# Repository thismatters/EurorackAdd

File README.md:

# Simple Add

This simple adder could come from any textbook which introduces op-amp circuits. Really simple, pretty useful too!

The KiCAD project here uses the library/footprints [found in my companion repo](https://github.com/thismatters/EurorackKiCAD).

## Width

7hp on an [Intellijel 1U rack](https://intellijel.com/support/1u-technical-specifications/).

## Inputs

Three signal jacks

## Outputs

One signal jack with the sum of the three inputs

## Vendors

There are part numbers in the [BOM](add.csv) for many of the parts (not for basic passives though) at the following vendors:

* [Mouser](https://www.mouser.com): Needs no introduction. Get your ICs from here (or [digikey](https://www.digikey.com)).
* [Tayda Electronics](https://www.taydaelectronics.com/): Good supplier for passive components; audio jacks, and potentiometers. Their audio jacks are slightly smaller than the thonkiconn from thonk.
* [Love My Switches](https://lovemyswitches.com/): Has [really good knobs](https://lovemyswitches.com/anodized-aluminum-knob-the-lo-fi-1-4-smooth-shaft-12-5mm-od/) to go on those potentiometers!
* [OSHPark](https://oshpark.com/): Fast and (relatively) cheap PCB manufacturer. Prototype run pending.

## Changelog

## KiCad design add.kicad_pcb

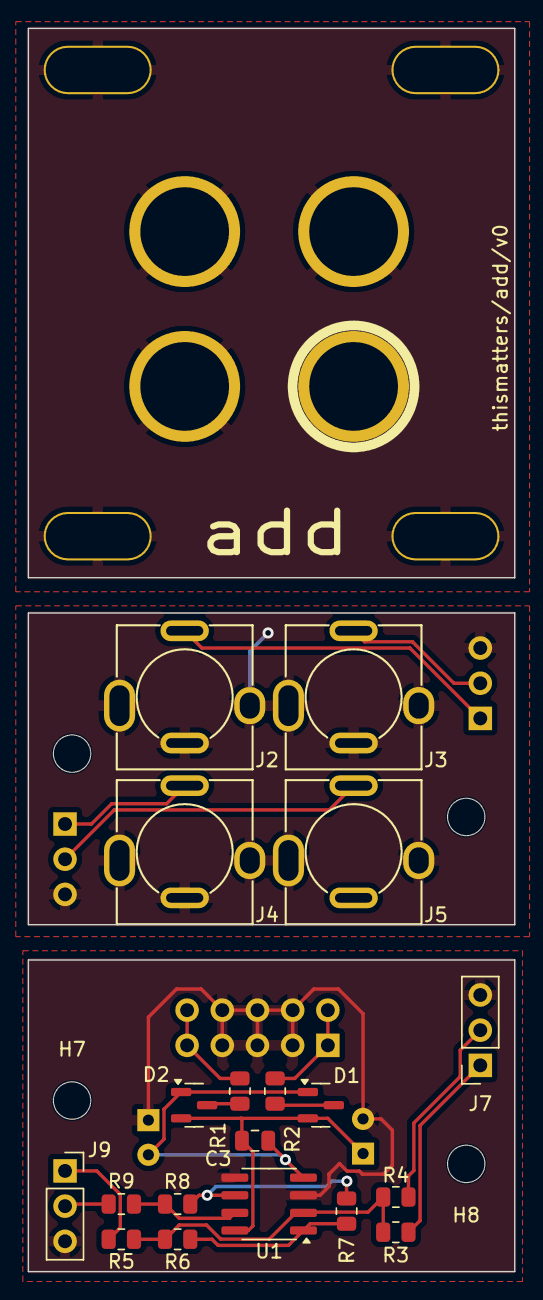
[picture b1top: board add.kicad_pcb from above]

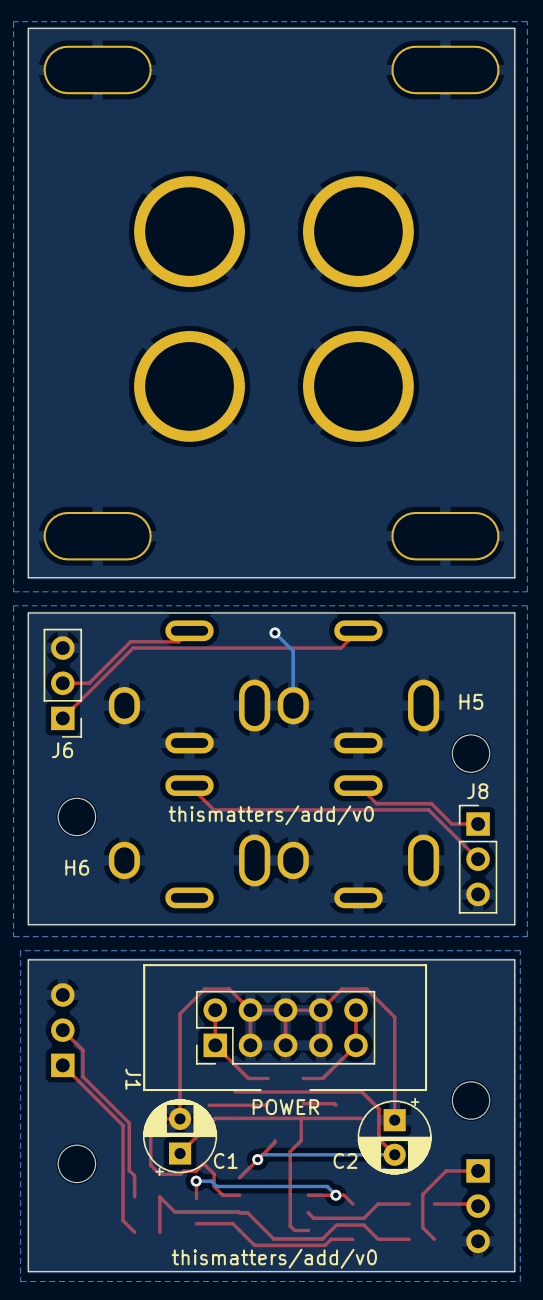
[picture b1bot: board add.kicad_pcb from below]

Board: 2 copper layers, 35.1 x 89.7 mm, 36 parts (7 on the bottom side), 21 nets.

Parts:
C1, C2: 22u 50V; CP_Radial_D5.0mm_P2.50mm
C3: 100n; C_0805_2012Metric
D1, D2: BAT54S; SOT-23
H1: mount0; Mech-MountingHole
H2, H3, H4: mount1; Mech-MountingHole
H5, H6, H7, H8: Standoff; MountingHole_2.7mm_M2.5
H9: in0; Mech-AudioJack-Hole-Input
H10: in1; Mech-AudioJack-Hole-Input
H11: in2; Mech-AudioJack-Hole-Input
H12: out; Mech-AudioJack-Hole-Output
J1: Conn_02x05_Odd_Even; PinHeader_2x05_P2.54mm_Vertical
J2: in0; AudioJack2_Tayda_A-2566
J3: in1; AudioJack2_Tayda_A-2566
J4: in2; AudioJack2_Tayda_A-2566
J5: out; AudioJack2_Tayda_A-2566
J6, J8: Conn_01x03_Pin; PinHeader_1x03_P2.54mm_Vertical
J7, J9: Conn_01x03_Socket; PinSocket_1x03_P2.54mm_Vertical
R1, R2: 10; R_0805_2012Metric
R3, R4, R5, R6, R7, R8: 100K; R_0805_2012Metric
R9: 1K; R_0805_2012Metric
U1: TL072; SOIC-8_3.9x4.9mm_P1.27mm

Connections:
+12V: C1.1, C3.1, D1.2 (K), D2.2 (K), U1.8 (V+)
-12V: C2.2, C3.2, D1.1 (A), D2.1 (A), U1.4 (V-)
/FACE: H1.1 (1_1), H2.1 (1_1), H3.1 (1_1), H4.1 (1_1), H9.1 (1_1), H10.1 (1_1), H11.1 (1_1), H12.1 (1_1)
/GND': J2.S, J2.TN, J3.S, J3.TN, J4.S, J4.TN, J5.S, J6.3, J8.3
/IN0: J2.T, J6.1
/IN0': J7.1, R3.1
/IN1: J3.T, J6.2
/IN1': J7.2, R4.1
/IN2: J4.T, J8.1
/IN2': J9.1, R5.1
/OUT: J5.T, J8.2
/OUT': J9.2, R9.1
GND: C1.2, C2.1, J1.3, J1.4, J1.5, J1.6, J1.7, J1.8, J7.3, J9.3, U1.3 (+), U1.5 (+)
unnamed: D1.3 (COM), R2.1
unnamed: D2.3 (COM), R1.1
unnamed: J1.1, J1.2, R2.2
unnamed: J1.9, J1.10, R1.2
unnamed: R6.2, R7.1, U1.1
unnamed: R8.2, R9.2, U1.7
unnamed: R3.2, R4.2, R5.2, R6.1, U1.2 (-)
unnamed: R7.2, R8.1, U1.6 (-)

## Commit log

2026-05-03 add bom
2026-05-03 update bom for sync
2026-05-03 fix capacitor value
2026-05-03 normal inputs to ground
